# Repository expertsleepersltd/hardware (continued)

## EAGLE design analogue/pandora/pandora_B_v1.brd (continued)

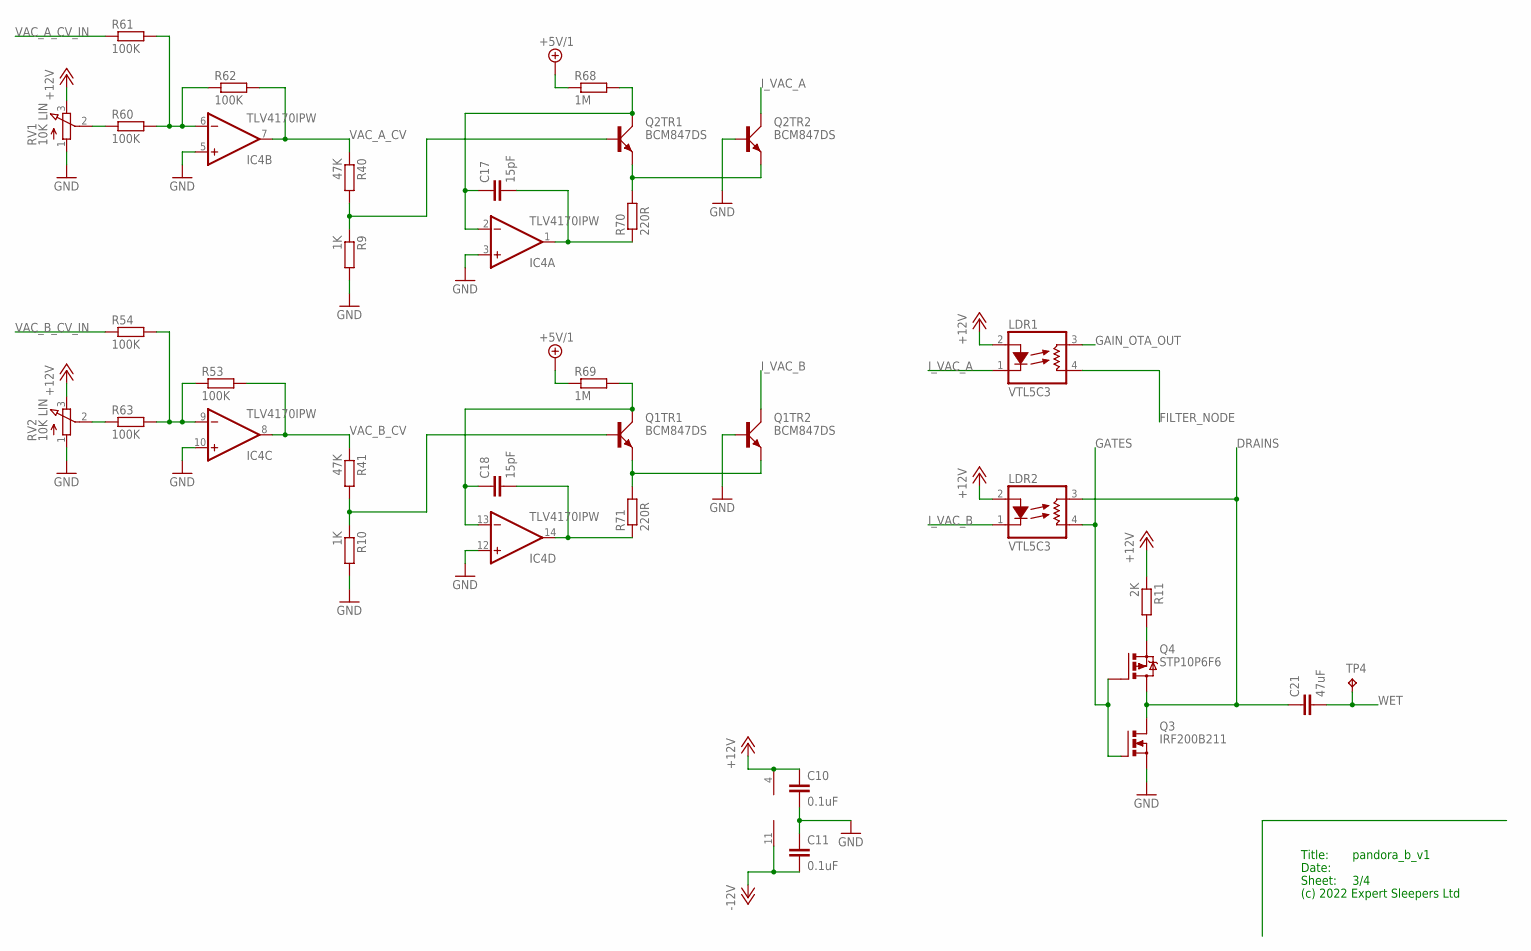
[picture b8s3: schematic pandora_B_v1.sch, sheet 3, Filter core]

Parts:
C10, C11: 0.1uF; C0402
C17, C18: 15pF; C0402
C21: 47uF; C1206
IC4: TLV4170IPW; PW_R-PDSO-G14
LDR1, LDR2: VTL5C3; VTL5C
Q1, Q2: BCM847DS; SOT95P275X110-6N
Q3: IRF200B211; TO220BV
Q4: STP10P6F6; TO220BV
R9, R10: 1K; R0603
R11: 2K; R1206
R40, R41: 47K; R0603
R53, R54, R60, R61, R62, R63: 100K; R0603
R68, R69: 1M; R0603
R70, R71: 220R; R0805
RV1, RV2: 10K LIN; RD1610NOA0X
TP4: RA2; P1-13

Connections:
+5V/1: R68.1, R69.1; also elsewhere on the board
+12V: C10.1, IC4.4 (V+), LDR1.2 (A), LDR2.2 (A), R11.1, RV1.3 (E), RV2.3 (E); also elsewhere on the board
-12V: C11.2, IC4.11 (V-); also elsewhere on the board
DRAINS: C21.1, LDR2.3 (L1), Q3.D, Q4.D; also elsewhere on the board
FILTER_NODE: LDR1.4 (L2); also elsewhere on the board
GAIN_OTA_OUT: LDR1.3 (L1); also elsewhere on the board
GATES: LDR2.4 (L2), Q3.G, Q4.G; also elsewhere on the board
GND: C10.2, C11.1, IC4.3 (+IN), IC4.5 (+IN), IC4.10 (+IN), IC4.12 (+IN), Q1.5 (B), Q2.5 (B), Q3.S, R9.2, R10.2, RV1.1 (A), RV2.1 (A); also elsewhere on the board
I_VAC_A: LDR1.1 (C), Q2.3 (C)
I_VAC_B: LDR2.1 (C), Q1.3 (C)
unnamed: R60.1, RV1.2 (S)
unnamed: IC4.6 (-IN), R60.2, R61.2, R62.1
unnamed: R63.1, RV2.2 (S)
unnamed: IC4.9 (-IN), R53.1, R54.2, R63.2
unnamed: Q2.2 (B), R9.1, R40.2
unnamed: C17.1, IC4.2 (-IN), Q2.6 (C), R68.2
unnamed: C17.2, IC4.1 (OUT), R70.1
unnamed: Q2.1 (E), Q2.4 (E), R70.2
unnamed: Q1.2 (B), R10.1, R41.2
unnamed: C18.1, IC4.13 (-IN), Q1.6 (C), R69.2
unnamed: C18.2, IC4.14 (OUT), R71.1
unnamed: Q1.1 (E), Q1.4 (E), R71.2
unnamed: Q4.S, R11.2
VAC_A_CV: IC4.7 (OUT), R40.1, R62.2
VAC_A_CV_IN: R61.1; also elsewhere on the board
VAC_B_CV: IC4.8 (OUT), R41.1, R53.2
VAC_B_CV_IN: R54.1; also elsewhere on the board
WET: C21.2, TP4.TP; also elsewhere on the board

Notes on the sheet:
Title:
Date:
Sheet:
(c) 2022 Expert Sleepers Ltd

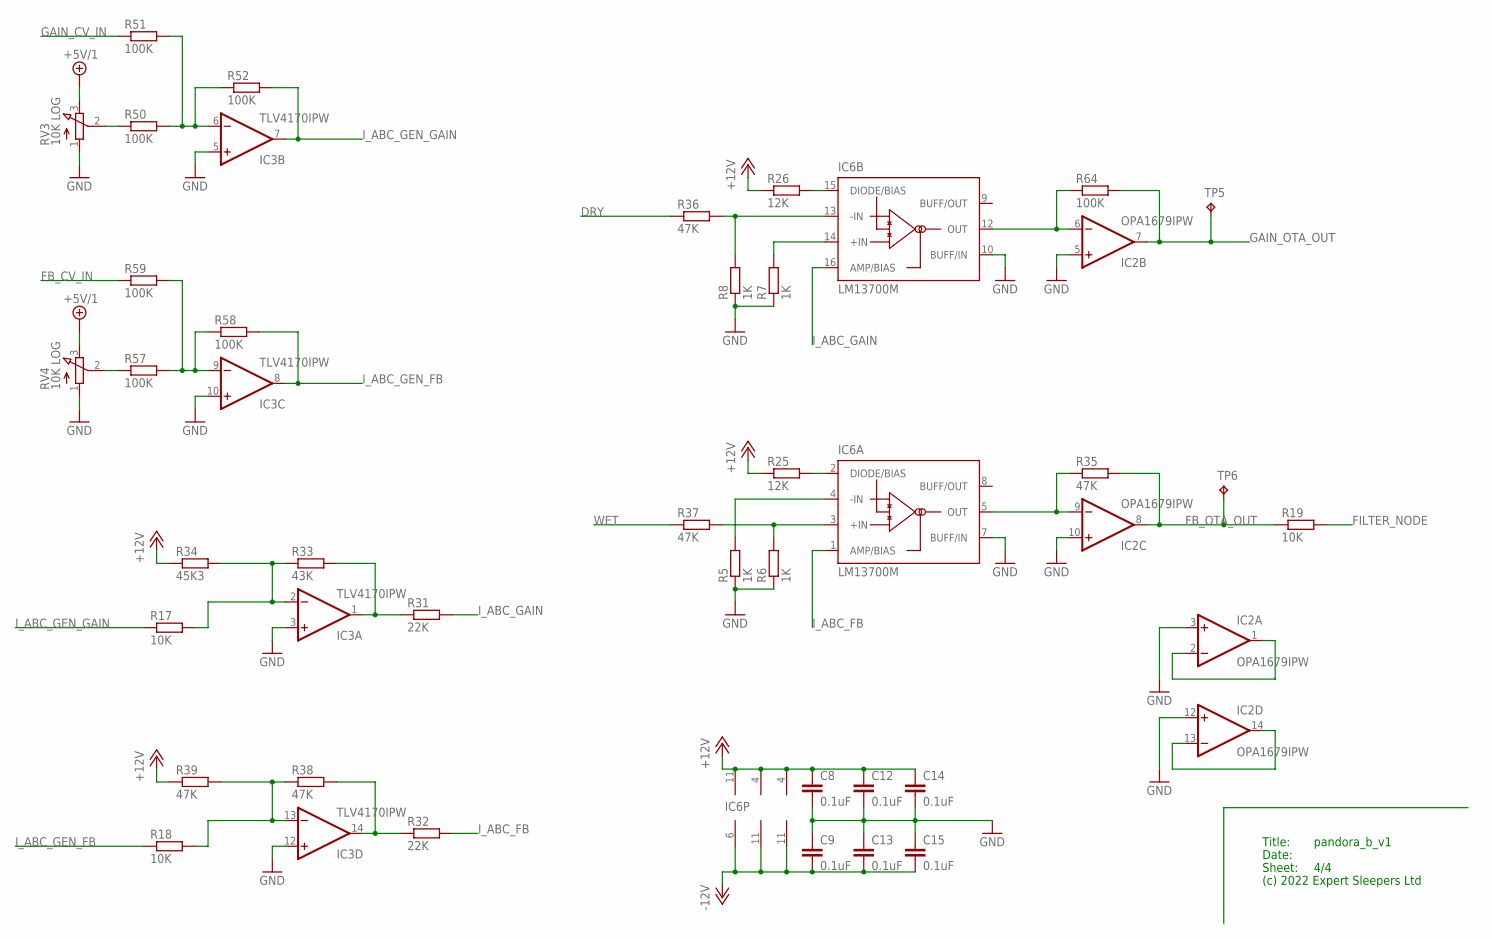
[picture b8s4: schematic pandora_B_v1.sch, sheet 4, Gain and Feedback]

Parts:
C8, C9, C12, C13, C14, C15: 0.1uF; C0402
IC2: OPA1679IPW; PW_R-PDSO-G14
IC3: TLV4170IPW; PW_R-PDSO-G14
IC6: LM13700M; SO16
R5, R6, R7, R8: 1K; R0603
R17, R18, R19: 10K; R0603
R25, R26: 12K; R0603
R31, R32: 22K; R0603
R33: 43K; R0603
R34: 45K3; R0603
R35, R36, R37, R38, R39: 47K; R0603
R50, R51, R52, R57, R58, R59, R64: 100K; R0603
RV3, RV4: 10K LOG; RD1610NOA0X
TP5, TP6: RA2; P1-13

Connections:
+5V/1: RV3.3 (E), RV4.3 (E); also elsewhere on the board
+12V: C8.1, C12.1, C14.1, IC2.4 (V+), IC3.4 (V+), IC6.11 (V+), R25.1, R26.1, R34.1, R39.1; also elsewhere on the board
-12V: C9.2, C13.2, C15.2, IC2.11 (V-), IC3.11 (V-), IC6.6 (V-); also elsewhere on the board
DRY: R36.1; also elsewhere on the board
FB_CV_IN: R59.1; also elsewhere on the board
FB_OTA_OUT: IC2.8 (OUT), R19.1, R35.2, TP6.TP
FILTER_NODE: R19.2; also elsewhere on the board
GAIN_CV_IN: R51.1; also elsewhere on the board
GAIN_OTA_OUT: IC2.7 (OUT), R64.2, TP5.TP; also elsewhere on the board
GND: C8.2, C9.1, C12.2, C13.1, C14.2, C15.1, IC2.3 (+IN), IC2.5 (+IN), IC2.10 (+IN), IC2.12 (+IN), IC3.3 (+IN), IC3.5 (+IN), IC3.10 (+IN), IC3.12 (+IN), IC6.7 (BUFF/IN), IC6.10 (BUFF/IN), R5.1, R6.1, R7.1, R8.1, RV3.1 (A), RV4.1 (A); also elsewhere on the board
I_ABC_FB: IC6.1 (AMP/BIAS), R32.2
I_ABC_GAIN: IC6.16 (AMP/BIAS), R31.2
I_ABC_GEN_FB: IC3.8 (OUT), R18.1, R58.2
I_ABC_GEN_GAIN: IC3.7 (OUT), R17.1, R52.2
unnamed: R57.1, RV4.2 (S)
unnamed: IC3.9 (-IN), R57.2, R58.1, R59.2
unnamed: IC6.15 (DIODE/BIAS), R26.2
unnamed: IC6.2 (DIODE/BIAS), R25.2
unnamed: IC2.9 (-IN), IC6.5 (OUT), R35.1
unnamed: IC2.6 (-IN), IC6.12 (OUT), R64.1
unnamed: IC2.1 (OUT), IC2.2 (-IN)
unnamed: IC2.13 (-IN), IC2.14 (OUT)
unnamed: IC6.3 (+IN), R6.2, R37.2
unnamed: IC6.4 (-IN), R5.2
unnamed: IC6.14 (+IN), R7.2
unnamed: IC6.13 (-IN), R8.2, R36.2
unnamed: R50.1, RV3.2 (S)
unnamed: IC3.6 (-IN), R50.2, R51.2, R52.1
unnamed: IC3.2 (-IN), R17.2, R33.1, R34.2
unnamed: IC3.1 (OUT), R31.1, R33.2
unnamed: IC3.14 (OUT), R32.1, R38.2
unnamed: IC3.13 (-IN), R18.2, R38.1, R39.2
WET: R37.1; also elsewhere on the board

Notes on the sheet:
Title:
Date:
Sheet:
(c) 2022 Expert Sleepers Ltd

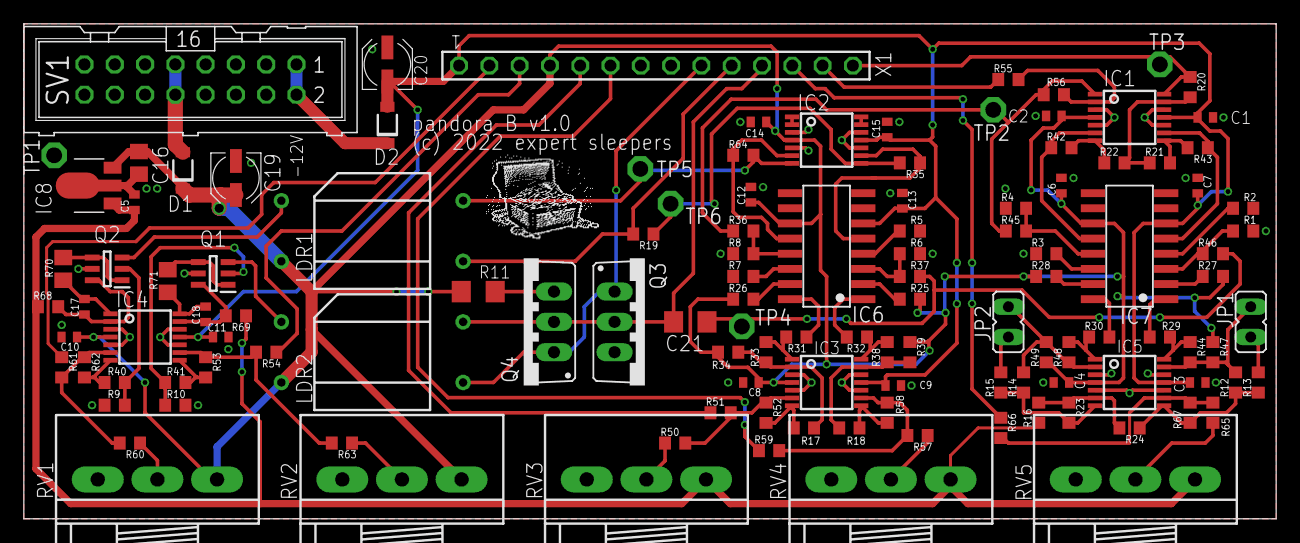
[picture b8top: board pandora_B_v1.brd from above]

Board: 2 copper layers, 105.0 x 41.5 mm, 124 parts (0 on the bottom side), 84 nets.

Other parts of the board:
U$2: TREASURE_10MM_300DPI

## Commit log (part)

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2021-06-18 Update README.md
    Added CC BY-SA 4.0
2021-06-24 added panels folder
2021-06-24 Update LICENSE.md
    Fixed formatting.
2021-06-24 Update README.md
    Made LICENSE.md a link to the license.
2021-06-24 added more panels
2021-06-24 renamed FH-2 to fh-2 for consistency
2021-06-24 Added the MIDI breakout
2021-07-01 added Tiny MIDI breakout
2021-09-08 Create esx-8cv-3hp.fpd
    3HP version of the FHX/ESX panel (contributed by Winter Cyan)
2021-09-08 Create esx-8cv-3hp.fpd
    3HP version of the ESX/FHX panel (contributed by Winter Cyan)
2021-09-08 3HP version of the ESX/FHX panel (contributed by Winter Cyan)
2021-10-11 added Ivo, Lorelei and Beatrix panels
2021-10-11 Added Ivo, Lorelei and Beatrix
2021-10-11 fixed READMEs which had somehow become swapped
2021-12-04 added disting mk2 panel
2021-12-15 Added Power Bus.
2022-05-20 Added 1U Display Adaptor
2022-06-09 typo
2022-06-09 Set theme jekyll-theme-slate
2022-06-09 Added disting_ex_display_connection.jpg
2022-06-15 Added css and link to forum
2022-06-30 Add power specs
2022-07-29 Added Persephone
2022-07-29 Fixed links to panels folder
2022-07-29 Added Persephone front panel
2022-11-22 added Pandora
2023-03-02 added Amelia
2023-03-13 Added link to Thonk
2023-07-12 added Aloysius
2023-09-26 Added Cicely
2024-02-26 Added Otterley.
2024-05-20 Added FH-1
2024-11-22 added disting NT panel
2024-12-09 Added disting NT pedablboard breakout
2026-06-03 Added NTX-8CV panel
